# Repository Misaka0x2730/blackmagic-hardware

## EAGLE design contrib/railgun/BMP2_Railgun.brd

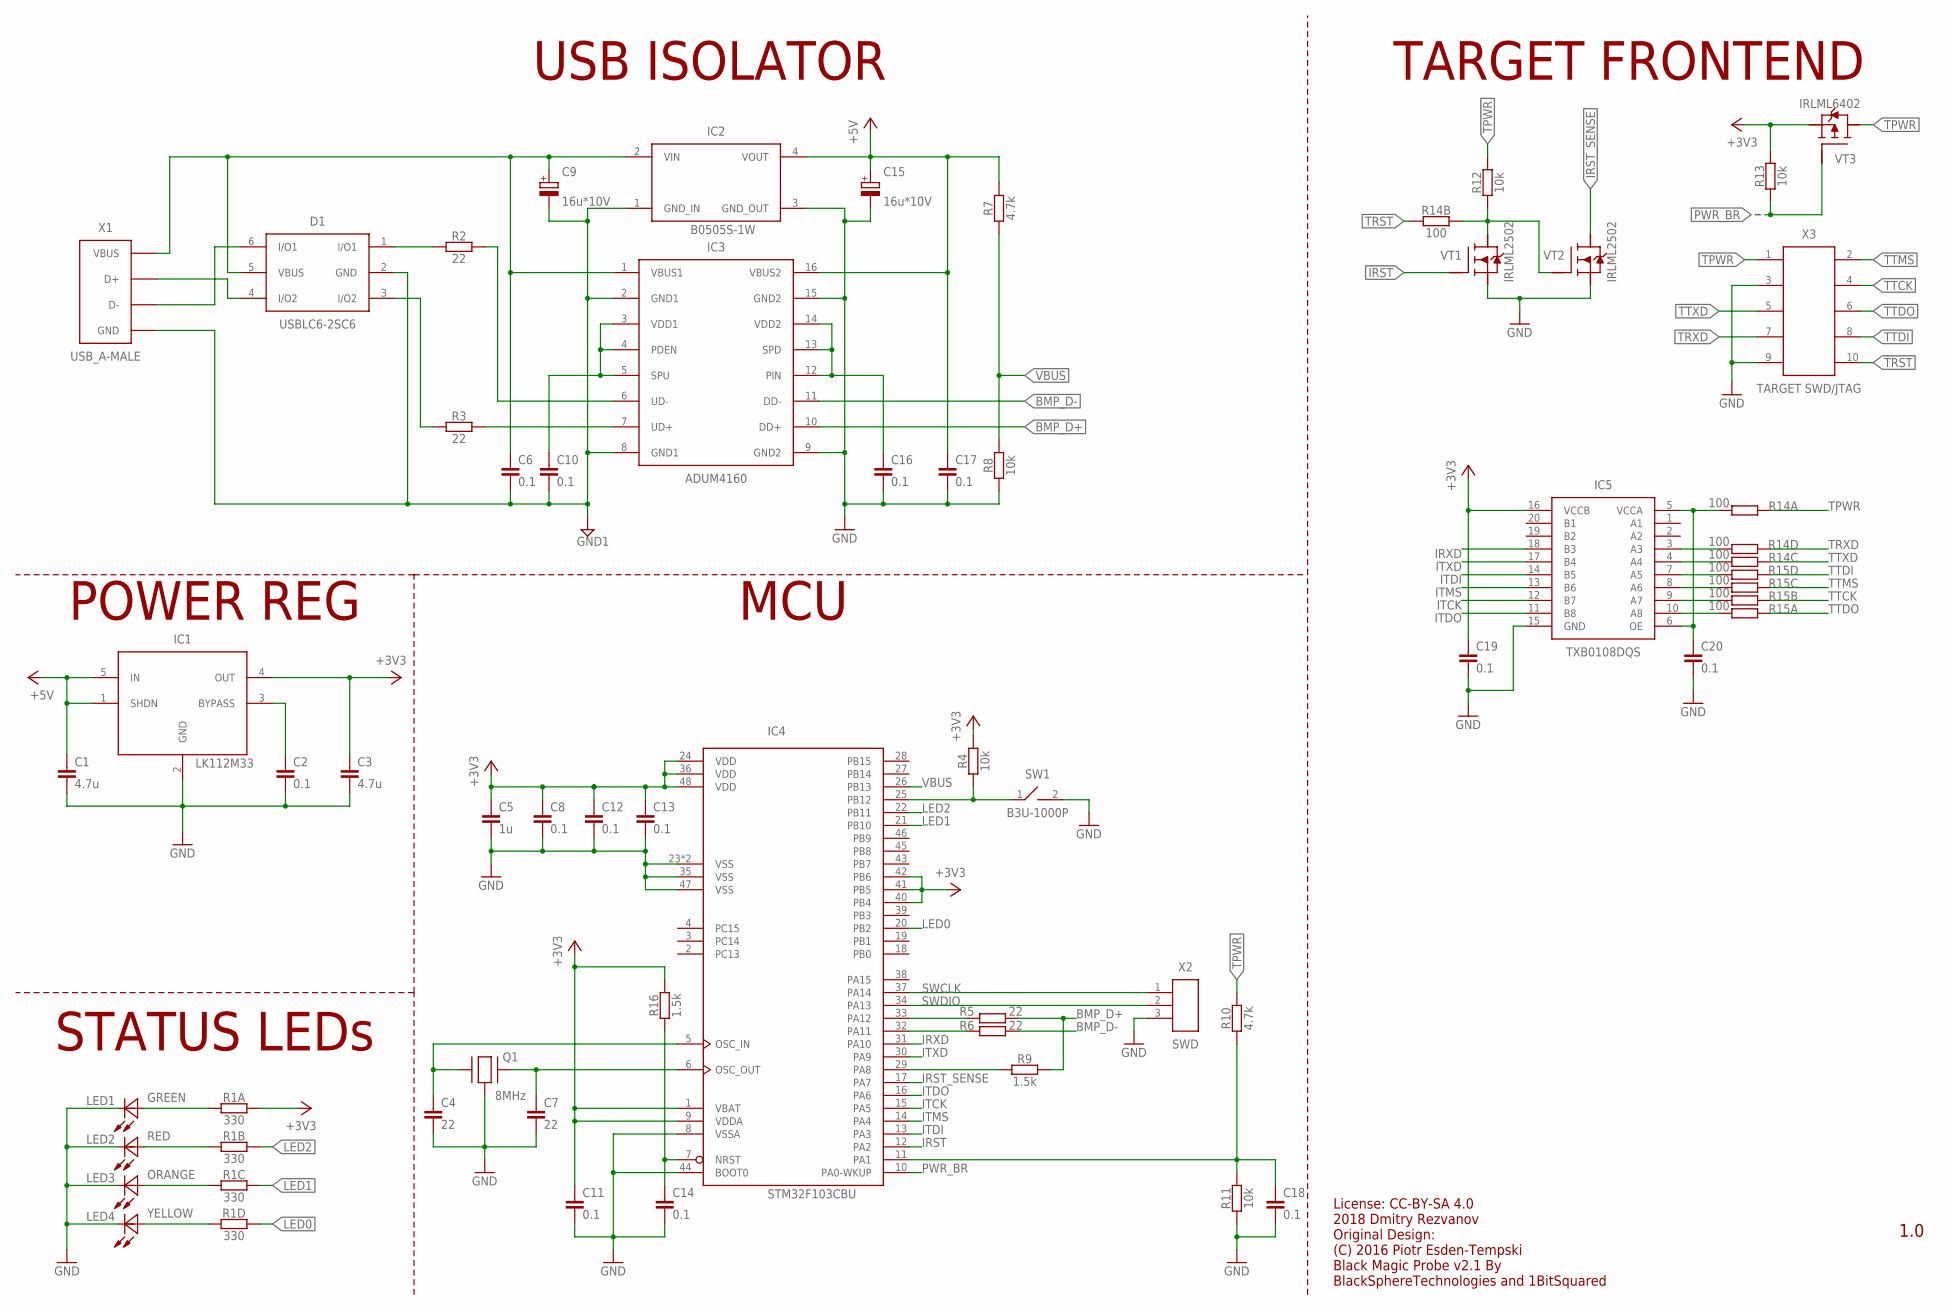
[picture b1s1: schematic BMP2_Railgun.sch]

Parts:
C1, C3: 4.7u; 0603
C2, C8, C10, C11, C12, C13, C14, C16, C18, C19, C20: 0.1; 0402
C4, C7: 22; 0402
C5: 1u; 0603
C6, C17: 0.1; 0603
C9, C15: 16u*10V; C3216/A
D1: USBLC6-2SC6; SOT23-6L
IC1: LK112M33; SOT23-5L
IC2: B0505S-1W; 4SIP
IC3: ADUM4160; SO-16W
IC4: STM32F103CBU; UFQFPN48
IC5: TXB0108DQS; PUSON-N20
LED1: GREEN; LED0603
LED2: RED; LED0603
LED3: ORANGE; LED0603
LED4: YELLOW; LED0603
Q1: 8MHz; 3225
R1: 330; ARRAY_0603
R2, R3, R5, R6: 22; 0402
R4, R8, R11, R12, R13: 10k; 0402
R7, R10: 4.7k; 0402
R9, R16: 1.5k; 0402
R14, R15: 100; ARRAY_0603
SW1: B3U-1000P
VT1, VT2: IRLML2502; SOT23
VT3: IRLML6402; SOT23
X1: USB_A-MALE; USB-A-MALE
X2: SWD; PH1X03_1.27
X3: TARGET SWD/JTAG; IDC-10(FACE)

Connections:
+3V3: C3.1, C5.1, C8.1, C11.1, C12.1, C13.1, C19.1, IC1.4 (OUT), IC4.1 (VBAT), IC4.9 (VDDA), IC4.24 (VDD), IC4.36 (VDD), IC4.40 (PB4), IC4.41 (PB5), IC4.42 (PB6), IC4.48 (VDD), IC5.16 (VCCB), R1.1, R4.1, R13.1, R16.1, VT3.2 (S)
+5V: C1.1, C15.2 (+), C17.1, IC1.1 (SHDN), IC1.5 (IN), IC2.4 (VOUT), IC3.16 (VBUS2), R7.1
BMP_D+: IC3.10 (DD+), R5.1, R9.1
BMP_D-: IC3.11 (DD-), R6.1
GND: C1.2, C2.2, C3.2, C4.2, C5.2, C7.2, C8.2, C11.2, C12.2, C13.2, C14.2, C15.1 (-), C16.2, C17.2, C18.2, C19.2, C20.2, IC1.2 (GND), IC2.3 (GND_OUT), IC3.9 (GND2), IC3.15 (GND2), IC4.8 (VSSA), IC4.23 (VSS), IC4.35 (VSS), IC4.44 (BOOT0), IC4.47 (VSS), IC4.49 (VSS), IC5.15 (GND), LED1.2 (C), LED2.2 (C), LED3.2 (C), LED4.2 (C), Q1.2 (GND), Q1.4 (GND), R8.2, R11.2, SW1.2, VT1.2 (S), VT2.2 (S), X2.3, X3.3, X3.9
GND1: C6.2, C9.1 (-), C10.2, D1.2 (GND), IC2.1 (GND_IN), IC3.2 (GND1), IC3.8 (GND1), X1.1 (GND), X1.GND@1 (GND), X1.GND@2 (GND)
IRST: IC4.12 (PA2), VT1.1 (G)
IRST_SENSE: IC4.17 (PA7), VT2.3 (D)
IRXD: IC4.31 (PA10), IC5.18 (B3)
ITCK: IC4.15 (PA5), IC5.12 (B7)
ITDI: IC4.13 (PA3), IC5.14 (B5)
ITDO: IC4.16 (PA6), IC5.11 (B8)
ITMS: IC4.14 (PA4), IC5.13 (B6)
ITXD: IC4.30 (PA9), IC5.17 (B4)
LED0: IC4.20 (PB2), R1.4 (1)
LED1: IC4.21 (PB10), R1.3 (1)
LED2: IC4.22 (PB11), R1.2 (1)
unnamed: D1.1 (I/O1), R2.1
unnamed: IC3.7 (UD+), R3.2
unnamed: D1.3 (I/O2), R3.1
unnamed: IC3.6 (UD-), R2.2
unnamed: IC4.32 (PA11), R6.2
unnamed: IC4.33 (PA12), R5.2
unnamed: C10.1, IC3.3 (VDD1), IC3.4 (PDEN), IC3.5 (SPU)
unnamed: D1.6 (I/O1), X1.3 (D-)
unnamed: IC4.25 (PB12), R4.2, SW1.1
unnamed: D1.4 (I/O2), X1.2 (D+)
unnamed: C16.1, IC3.12 (PIN), IC3.13 (SPD), IC3.14 (VDD2)
unnamed: C7.1, IC4.6 (OSC_OUT), Q1.3 (2)
unnamed: C4.1, IC4.5 (OSC_IN), Q1.1
unnamed: LED1.1 (A), R1.8 (2)
unnamed: C6.1, C9.2 (+), D1.5 (VBUS), IC2.2 (VIN), IC3.1 (VBUS1), X1.4 (VBUS)
unnamed: LED4.1 (A), R1.5 (2)
unnamed: LED3.1 (A), R1.6 (2)
unnamed: LED2.1 (A), R1.7 (2)
unnamed: C2.1, IC1.3 (BYPASS)
unnamed: R12.1, R14.2 (1), VT1.3 (D), VT2.1 (G)
unnamed: IC4.29 (PA8), R9.2
unnamed: C20.1, IC5.5 (VCCA), IC5.6 (OE), R14.1
unnamed: C18.1, IC4.11 (PA1), R10.2, R11.1
unnamed: IC5.10 (A8), R15.1
unnamed: IC5.9 (A7), R15.2 (1)
unnamed: IC5.8 (A6), R15.3 (1)
unnamed: IC5.7 (A5), R15.4 (1)
unnamed: IC5.4 (A4), R14.3 (1)
unnamed: IC5.3 (A3), R14.4 (1)
PWR_BR: IC4.10 (PA0-WKUP), R13.2, VT3.1 (G)
RST: C14.1, IC4.7 (NRST), R16.2
SWCLK: IC4.37 (PA14), X2.1
SWDIO: IC4.34 (PA13), X2.2
TPWR: R10.1, R12.2, R14.8 (2), VT3.3 (D), X3.1
TRST: R14.7 (2), X3.10
TRXD: R14.5 (2), X3.7
TTCK: R15.7 (2), X3.4
TTDI: R15.5 (2), X3.8
TTDO: R15.8 (2), X3.6
TTMS: R15.6 (2), X3.2
TTXD: R14.6 (2), X3.5
VBUS: IC4.26 (PB13), R7.2, R8.1

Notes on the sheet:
USB ISOLATOR
POWER REG
STATUS LEDs
TARGET FRONTEND
MCU
License: CC-BY-SA 4.0 2018 Dmitry Rezvanov Original Design: (C) 2016 Piotr Esden-Tempski Black Magic Probe v2.1 By BlackSphereTechnologies and 1BitSquared
1.0

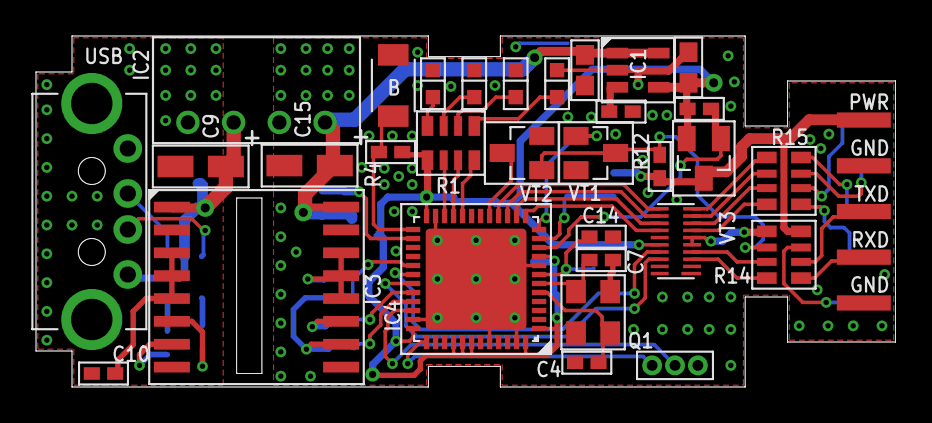
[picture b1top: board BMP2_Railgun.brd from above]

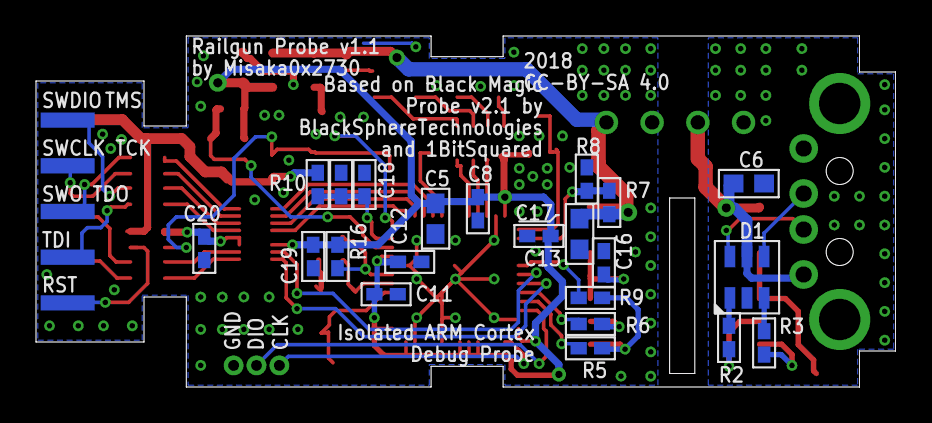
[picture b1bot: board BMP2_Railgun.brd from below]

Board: 2 copper layers, 47.8 x 19.5 mm, 54 parts (22 on the bottom side), 59 nets.

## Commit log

2018-01-02 Fixed errors in angle of line.
2018-01-03 Fixed bug with single node in the net XRST.
2018-01-05 Fixed error in position of USB connector.
2018-01-05 Fixed board outline..
2018-01-19 Fixed board size.
2018-06-26 New board version.
